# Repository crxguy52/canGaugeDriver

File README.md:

Software to use [CANBed FD](https://www.seeedstudio.com/CANBed-FD-Arduino-CAN-FD-Development-Kit-p-4724.html) to read CAN data and drive gauges on a NB Miata

Used in conjunction with the [baseboard](https://github.com/crxguy52/canGagueDriver-baseBoard) to convert signals from 12 to 5V and vice versa

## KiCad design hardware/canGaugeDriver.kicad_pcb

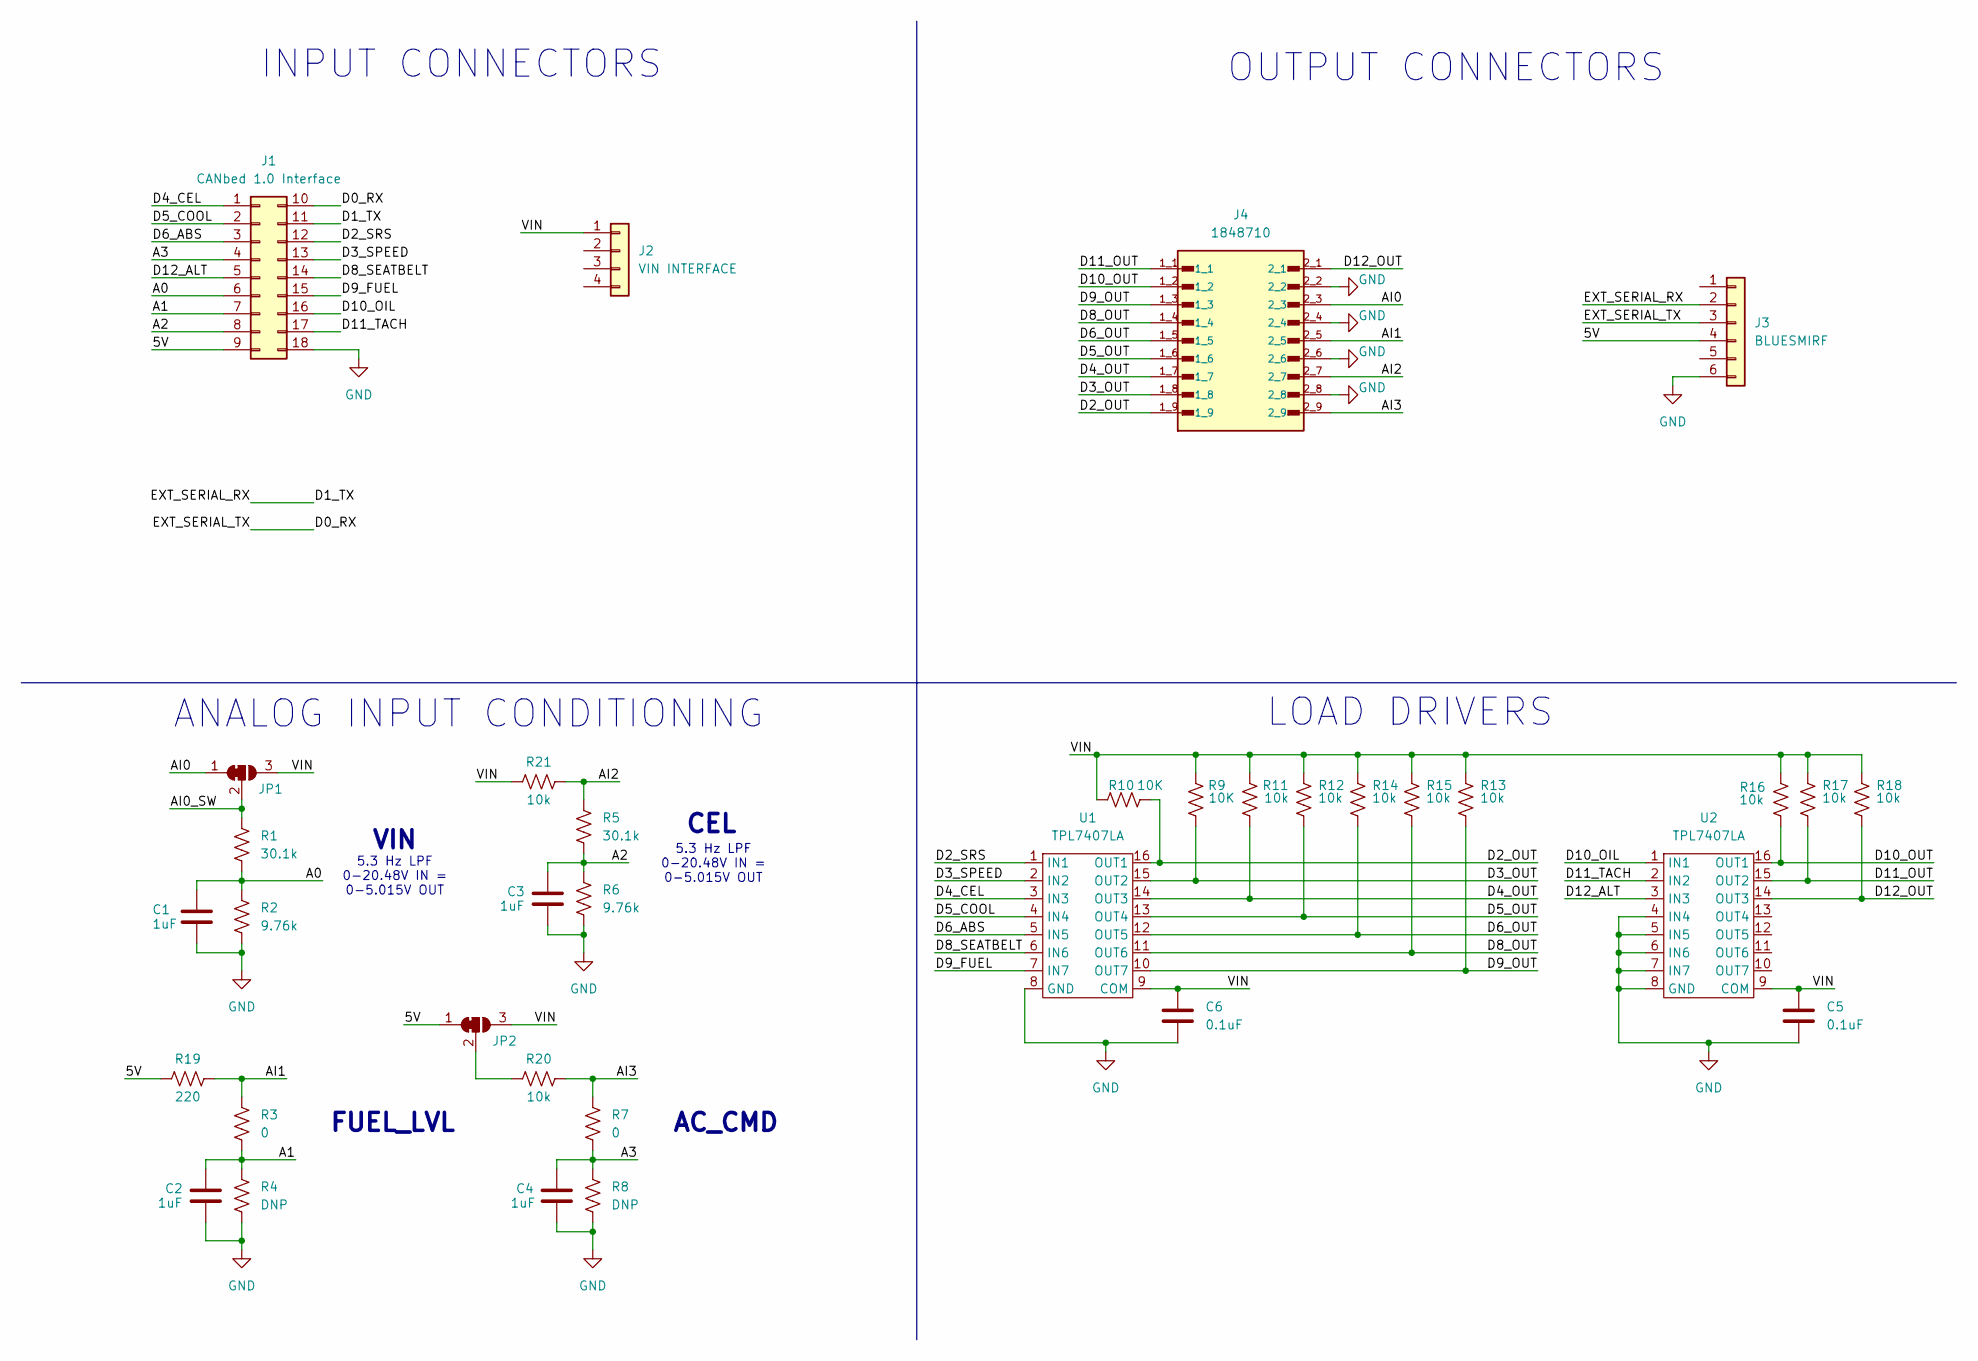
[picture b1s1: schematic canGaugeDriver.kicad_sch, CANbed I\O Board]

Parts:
C1, C2, C3, C4: 1uF; C_1206_3216Metric_Pad1.33x1.80mm_HandSolder
C5, C6: 0.1uF; C_1206_3216Metric_Pad1.33x1.80mm_HandSolder
J1: CANbed 1.0 Interface; PinHeader_2x09_P2.54mm_Vertical
J2: VIN INTERFACE; VIN_Pins
J3: BLUESMIRF; PinHeader_1x06_P2.54mm_Vertical
J4: 1848710; PHOENIX_1848710; PARTREV 11.07.2018
JP1, JP2: SolderJumper_3_Open; SolderJumper-3_P1.3mm_Open_Pad1.0x1.5mm_NumberLabels
R1, R5: 30.1k; R_1206_3216Metric_Pad1.30x1.75mm_HandSolder
R2, R6: 9.76k; R_1206_3216Metric_Pad1.30x1.75mm_HandSolder
R3, R7: 0; R_1206_3216Metric_Pad1.30x1.75mm_HandSolder
R4, R8: DNP; R_1206_3216Metric_Pad1.30x1.75mm_HandSolder
R9, R10: 10K; R_0805_2012Metric_Pad1.20x1.40mm_HandSolder
R11, R12, R13, R14, R15, R16, R17, R18, R20, R21: 10k; R_0805_2012Metric_Pad1.20x1.40mm_HandSolder
R19: 220; R_2512_6332Metric
U1, U2: TPL7407LA; SOIC-16_3.9x9.9mm_P1.27mm

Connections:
/5V: J1.9, J3.4, JP2.1 (A), R19.2
/A0: C1.1, J1.6, R1.2, R2.1
/A1: C2.1, J1.7, R3.2, R4.1
/A2: C3.1, J1.8, R5.2, R6.1
/A3: C4.1, J1.4, R7.2, R8.1
/AI0: J4.2_3, JP1.1 (A)
/AI0_SW: JP1.2 (C), R1.1
/AI1: J4.2_5, R3.1, R19.1
/AI2: J4.2_7, R5.1, R21.1
/AI3: J4.2_9, R7.1, R20.1
/D0_RX: J1.10, J3.3
/D1_TX: J1.11, J3.2
/D2_OUT: J4.1_9, R10.2, U1.16 (OUT1)
/D2_SRS: J1.12, U1.1 (IN1)
/D3_OUT: J4.1_8, R9.2, U1.15 (OUT2)
/D3_SPEED: J1.13, U1.2 (IN2)
/D4_CEL: J1.1, U1.3 (IN3)
/D4_OUT: J4.1_7, R11.2, U1.14 (OUT3)
/D5_COOL: J1.2, U1.4 (IN4)
/D5_OUT: J4.1_6, R12.2, U1.13 (OUT4)
/D6_ABS: J1.3, U1.5 (IN5)
/D6_OUT: J4.1_5, R14.2, U1.12 (OUT5)
/D8_OUT: J4.1_4, R15.2, U1.11 (OUT6)
/D8_SEATBELT: J1.14, U1.6 (IN6)
/D9_FUEL: J1.15, U1.7 (IN7)
/D9_OUT: J4.1_3, R13.2, U1.10 (OUT7)
/D10_OIL: J1.16, U2.1 (IN1)
/D10_OUT: J4.1_2, R16.2, U2.16 (OUT1)
/D11_OUT: J4.1_1, R17.2, U2.15 (OUT2)
/D11_TACH: J1.17, U2.2 (IN2)
/D12_ALT: J1.5, U2.3 (IN3)
/D12_OUT: J4.2_1, R18.2, U2.14 (OUT3)
/VIN: C5.1, C6.1, J2.1 (Pin_1_1), JP1.3 (B), JP2.3 (B), R9.1, R10.1, R11.1, R12.1, R13.1, R14.1, R15.1, R16.1, R17.1, R18.1, R21.2, U1.9 (COM), U2.9 (COM)
GND: C1.2, C2.2, C3.2, C4.2, C5.2, C6.2, J1.18, J3.6, J4.2_2, J4.2_4, J4.2_6, J4.2_8, R2.2, R4.2, R6.2, R8.2, U1.8 (GND), U2.4 (IN4), U2.5 (IN5), U2.6 (IN6), U2.7 (IN7), U2.8 (GND)
unnamed: JP2.2 (C), R20.2

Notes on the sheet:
5.3 Hz LPF 0-20.48V IN = 0-5.015V OUT
INPUT CONNECTORS
ANALOG INPUT CONDITIONING
AC_CMD
VIN
CEL
LOAD DRIVERS
OUTPUT CONNECTORS
FUEL_LVL

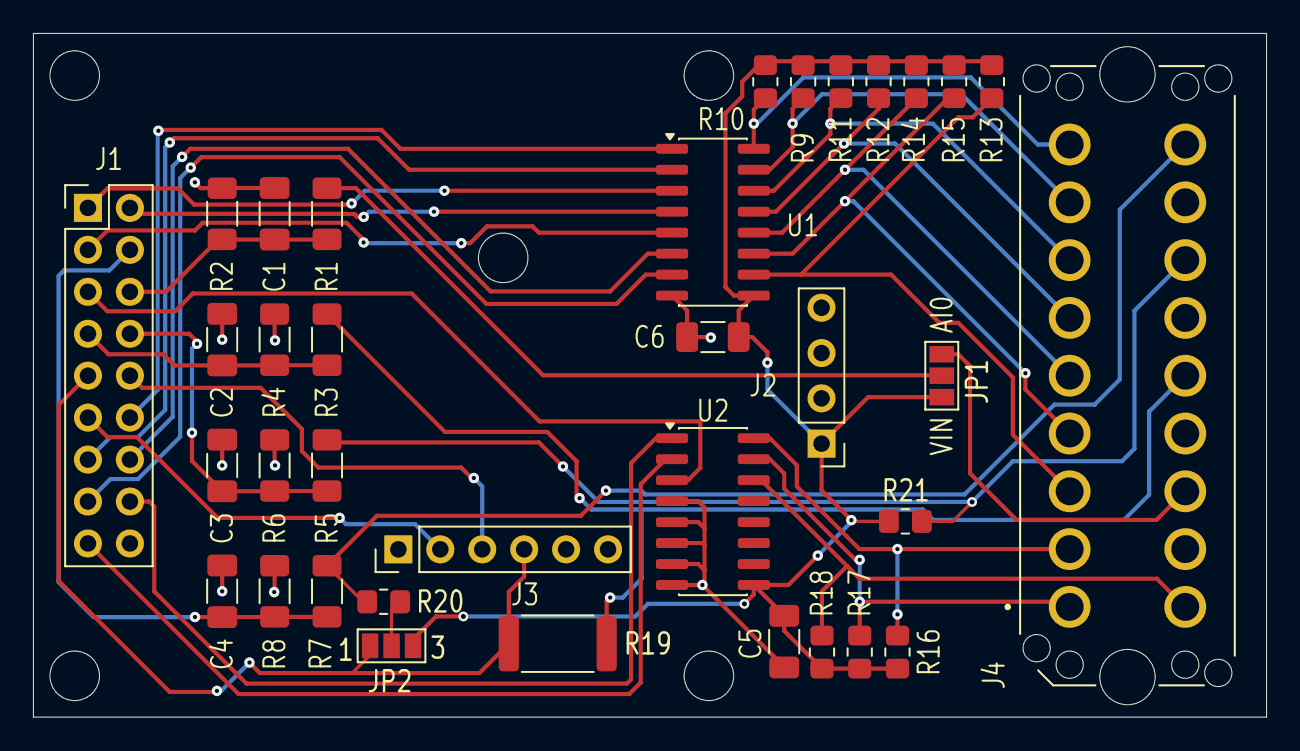
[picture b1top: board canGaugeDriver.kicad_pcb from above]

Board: 2 copper layers, 74.7 x 41.4 mm, 35 parts (0 on the bottom side), 35 nets.

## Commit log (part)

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2025-03-21 Mostly functional, need to test with cluster
2025-04-11 bus voltage transmit now working
